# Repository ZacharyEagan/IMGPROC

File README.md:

# IMGPROC
For all work primarily related to image processing or computer vision

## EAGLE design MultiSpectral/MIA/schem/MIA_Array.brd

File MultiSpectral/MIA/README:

Multispectral Identification Array

Zachary Eagan
Officially Begun:       Monday 1/02/2017
Expected Completion :   June 2017 

The MultiSpectral Identification Array (MIA) is an attempt to produce
usefull visible light spectrum data for a full image using a series of
known illumination sources. 

Hardware:
MIA attempts to reduce the cost and increase the spectral resolution 
of full image multispectral capture. By combining a large number of 
overlaping broad spectrum filters instead of narrow band emission 
sources, MIA can take advantage of inexpensive white light sources and
commonly available filters. 

The current hardware is a logitech C920 or similar opencv compatible 
camera, an array of 7 color LED's an arduino mega1280 to control the
LED's and a cheap  HP laptop. 

Software:
MIA is based on opencv's image capture and processing functionality.
Images are synchronised with the illumination sources via serial coms.
images are written to file once every full cycle of the lighting array
Array Camera syncronisation, and image processing are handled by 
seperate threads.
Spectrum data is output to screan via gnuplot. Later versions will
attempt to build an output image displaying only known materials based
on a database of sampled spectra.

Currently most functionality is implimented in various forms but not
integrated into the main program. 
Current work focusses on this integration.

bin     --executables go here
build   --object files
doc     --documentation
include --header files
lib     --additional libraries needed
spike   --functions under dev which have not been integrated
test    --program tests go here

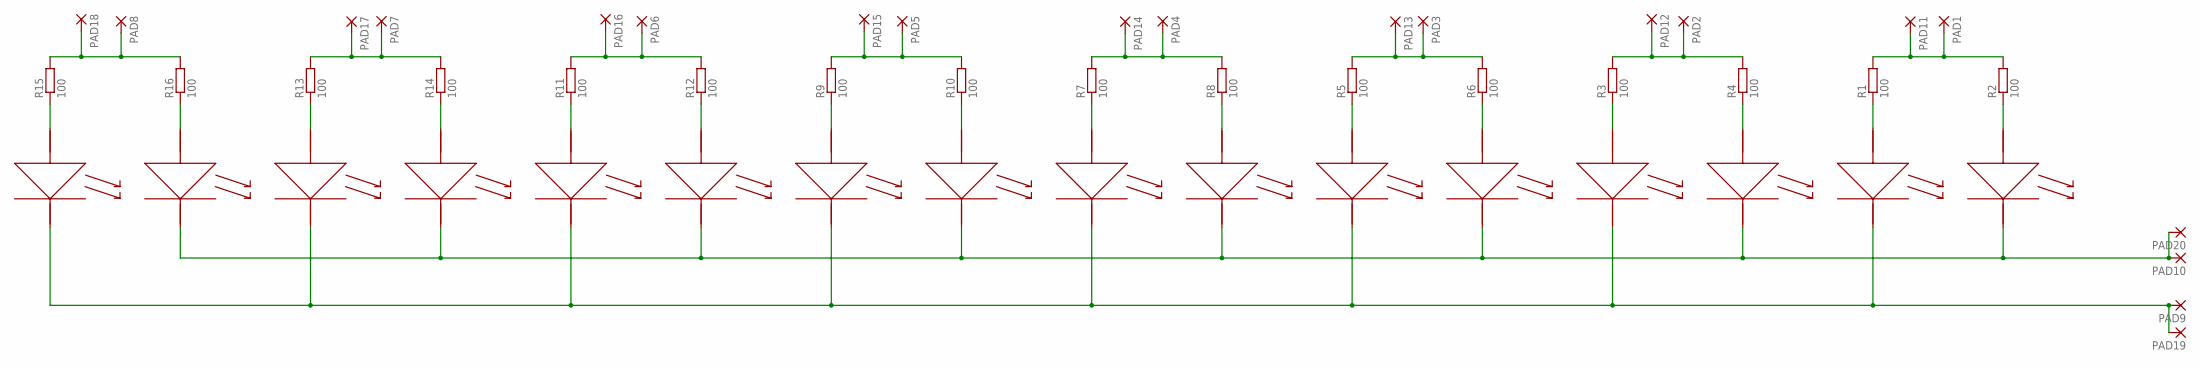
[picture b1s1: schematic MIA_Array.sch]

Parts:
PAD1, PAD2, PAD3, PAD4, PAD5, PAD6, PAD7, PAD8, PAD9, PAD10, PAD11, PAD12, PAD13, PAD14, PAD15, PAD16, PAD17, PAD18, PAD19, PAD20: 2,54/1,1
R1, R2, R3, R4, R5, R6, R7, R8, R9, R10, R11, R12, R13, R14, R15, R16: 100; 0411/15
U$1, U$2, U$3, U$4, U$5, U$6, U$7, U$8, U$9, U$10, U$11, U$12, U$13, U$14, U$15, U$16: L150-3080502400000; SMD-5050

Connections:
unnamed: PAD1.1, PAD11.1, R1.2, R2.2
unnamed: PAD10.1, PAD20.1, U$2.CA, U$2.CA2 (CA), U$5.CA, U$5.CA2 (CA), U$7.CA, U$7.CA2 (CA), U$9.CA, U$9.CA2 (CA), U$11.CA, U$11.CA2 (CA), U$12.CA, U$12.CA2 (CA), U$14.CA, U$14.CA2 (CA), U$16.CA, U$16.CA2 (CA)
unnamed: R1.1, U$4.AN, U$4.AN2 (AN)
unnamed: R2.1, U$12.AN, U$12.AN2 (AN)
unnamed: PAD2.1, PAD12.1, R3.2, R4.2
unnamed: R3.1, U$1.AN, U$1.AN2 (AN)
unnamed: R4.1, U$2.AN, U$2.AN2 (AN)
unnamed: PAD3.1, PAD13.1, R5.2, R6.2
unnamed: R5.1, U$3.AN, U$3.AN2 (AN)
unnamed: R6.1, U$5.AN, U$5.AN2 (AN)
unnamed: PAD9.1, PAD19.1, U$1.CA, U$1.CA2 (CA), U$3.CA, U$3.CA2 (CA), U$4.CA, U$4.CA2 (CA), U$6.CA, U$6.CA2 (CA), U$8.CA, U$8.CA2 (CA), U$10.CA, U$10.CA2 (CA), U$13.CA, U$13.CA2 (CA), U$15.CA, U$15.CA2 (CA)
unnamed: PAD4.1, PAD14.1, R7.2, R8.2
unnamed: R7.1, U$6.AN, U$6.AN2 (AN)
unnamed: R8.1, U$7.AN, U$7.AN2 (AN)
unnamed: PAD5.1, PAD15.1, R9.2, R10.2
unnamed: R9.1, U$8.AN, U$8.AN2 (AN)
unnamed: R10.1, U$9.AN, U$9.AN2 (AN)
unnamed: PAD6.1, PAD16.1, R11.2, R12.2
unnamed: R11.1, U$10.AN, U$10.AN2 (AN)
unnamed: R12.1, U$11.AN, U$11.AN2 (AN)
unnamed: PAD7.1, PAD17.1, R13.2, R14.2
unnamed: R13.1, U$13.AN, U$13.AN2 (AN)
unnamed: R14.1, U$14.AN, U$14.AN2 (AN)
unnamed: PAD8.1, PAD18.1, R15.2, R16.2
unnamed: R15.1, U$15.AN, U$15.AN2 (AN)
unnamed: R16.1, U$16.AN, U$16.AN2 (AN)

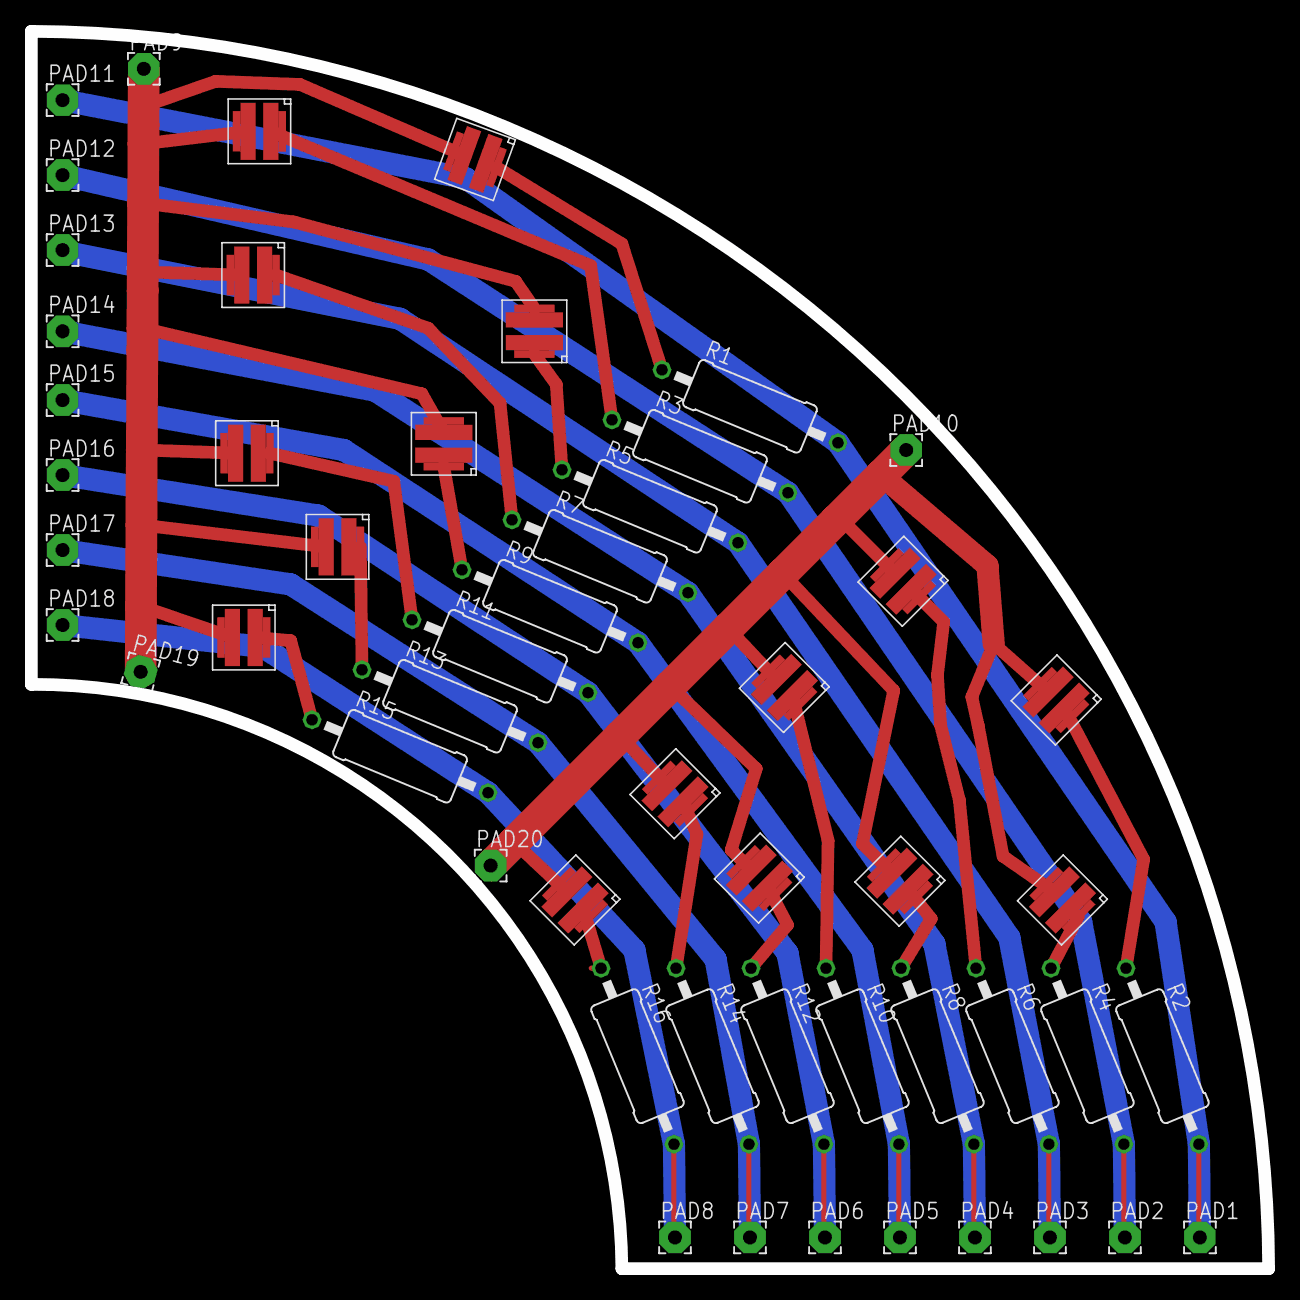
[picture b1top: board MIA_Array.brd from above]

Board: 2 copper layers, 99.0 x 99.0 mm, 52 parts (0 on the bottom side), 26 nets.

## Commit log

2017-03-13 Started Repository for image processing. Copied in some previous work.
2017-03-15 Added copy of TEST 17 which is a multi-threaded version of the camera/array
2017-03-24 Added ambiant light filter and increades exposure time
2017-04-08 Reorganised to a more usable file structure
2017-04-08 Moved older less organised files to PoorOrganisation
2017-04-08 Added new organisation system and updated makefile to match
2017-04-08 Starting to break threads out into a seperate file (probably broke it)
2017-04-10 Added a Data directory with sample data from ten minutes with a VLSpectrometer
2017-04-18 Altered Array initialisation to remove segfaults
2017-04-18 Reorganised threading, array and cam synced in one thread.buffer handled. fast
2017-04-24 Re-Synchronised Lights to Camera, at nearly 20fps. Good enough. WORKING
2017-04-24 Added file saving to cameraArrayThread. recorded video. lowered FR.
2017-04-24 Moved saving to file from the image capture thread to main. small FR increase
2017-04-24 Started Skeleton for ImgProc Thread
2017-04-25 Added thread to handle saving images. altered the mutex's to array
2017-04-26 removed the main saveing in prep for the saveThread
2017-04-30 Added schematic dir to hold circuit eliments and added L150 lib written on Fri
2017-05-04 Schematic files fleshed out, about to mill in a few minutes
2017-05-04 updated schematic boarders
2017-05-04 Moved pad20 closer to edge to avoid conflict with center anode trace
2017-05-08 Redid parts of ArrayComs to allow LED_ENV > 10 but something feels hacked
2017-11-17 Python image capture write and display
